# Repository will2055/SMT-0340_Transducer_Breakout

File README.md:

# SMT-0340_Transducer_Breakout
Surface mount transducer breakout

#### SMT-0340

SMT-0340-T-R, the smallest surface mount transducerever created! This tiny device is less than 1/6th the size of a dime and is perfect for generating audible notifications on wearables and other small electronics.

Datasheet: https://www.puiaudio.com/media/SpecSheet/SMT-0340-T-R.pdf

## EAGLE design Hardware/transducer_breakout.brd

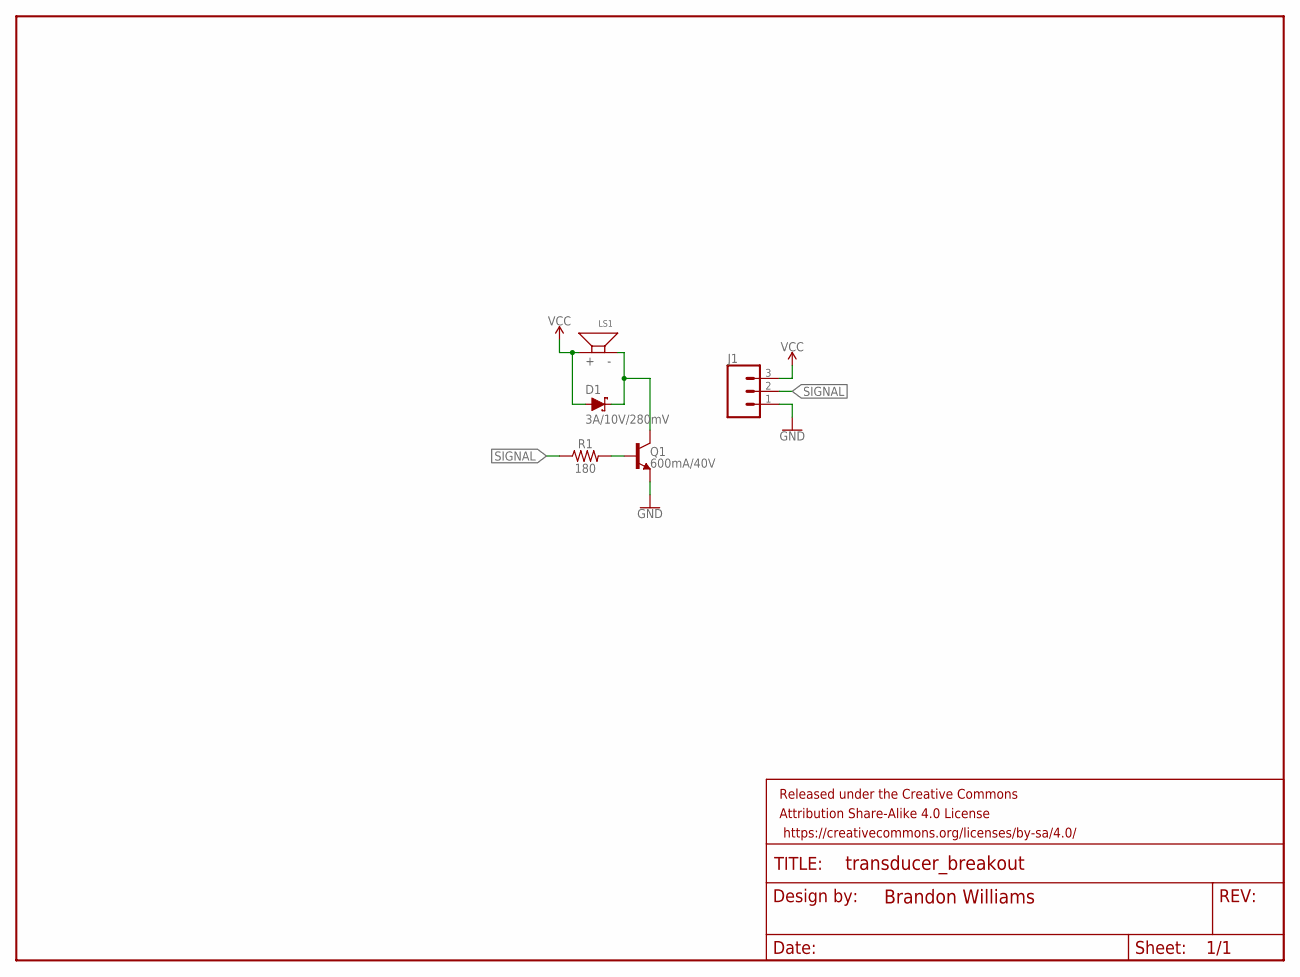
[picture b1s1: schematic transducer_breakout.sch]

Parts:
D1: 3A/10V/280mV; SOD-323
FRAME1: FRAME-LETTERNO_PACKAGE; DUMMY
J1: 455-1750-1-ND; 1X03
LS1: TRANSDUCERSMT-0340-T-R; SMT-0340-T-R
Q1: 600mA/40V; SOT23-3
R1: 180; 0603

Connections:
GND: J1.1, Q1.2 (E)
unnamed: D1.C, LS1.P$1 (-), Q1.3 (C)
unnamed: Q1.1 (B), R1.2
SIGNAL: J1.2, R1.1
VCC: D1.A, J1.3, LS1.P$2 (+)

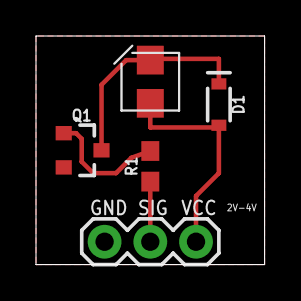
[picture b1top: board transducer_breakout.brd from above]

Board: 2 copper layers, 12.7 x 12.7 mm, 6 parts (0 on the bottom side), 5 nets.

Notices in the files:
parts and their libraries:
SparkFun-DiscreteSemi: Licensing: Creative Commons ShareAlike 4.0 International - https://creativecommons.org/licenses/by-sa/4.0
SparkFun-Aesthetics: Released under the Creative Commons Attribution Share-Alike 4.0 License
SparkFun-Aesthetics: https://creativecommons.org/licenses/by-sa/4.0
